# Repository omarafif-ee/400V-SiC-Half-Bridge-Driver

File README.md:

# 400 V SiC MOSFET Isolated Half-Bridge Gate Driver PCB

## Overview

**Objective:** To design a two-layer PCB for an isolated 400 V SiC MOSFET half-bridge gate driver using the UCC21520DW, with appropriate isolation, gate-drive control, and dead time. The design will be checked in KiCad and its switching behaviour verified through LTspice simulation.

This project covers the design and simulation of a 400 V isolated half-bridge gate driver using KiCad 10.0 and LTspice 26.1. A Texas Instruments UCC21520DW isolated dual-channel gate driver controls two Wolfspeed C3M0120090D 900 V SiC MOSFETs.

📄 **[Read the Full Technical Report (PDF)](Documentation/Technical%20Report%20-%20400V%20SiC%20MOSFET%20Isolated%20Half-Bridge%20Gate%20Driver%20PCB.pdf)**

---

## System Block Diagram

The 5 V PWM inputs (PWM-A and PWM-B) are separated from the 400 V power stage by the 5.7 kVrms isolation barrier inside the UCC21520DW. On the secondary side, the driver switches Q1 and Q2 across the 400 V DC rail and GNDPWR to swing SW_NODE between 0 V and 400 V, using a bootstrap network to power the floating high-side drive.

---

## Key Specifications

- DC bus voltage: 400 V DC
- Power switches: 2 × Wolfspeed C3M0120090D 900 V SiC MOSFETs in TO-247-3 packages
- Gate driver: Texas Instruments UCC21520DW, with a stated isolation rating of 5.7 kVrms
- Gate-drive supply: +15 V, with a bootstrap network for the floating high-side supply
- Hardware dead time: Approximately 220 ns, set using R1 = 22 kΩ
- PCB: Two copper layers
- High-voltage clearance rule: Custom KiCad design rule set to 2.9 mm for DC_PLUS and SW_NODE against other nets, with an exception for connections within the same floating high-side section

---

## Hardware Design and PCB Layout

### 1. Schematic

The UCC21520DW isolates the logic ground (GND) from the power-side connections (GNDPWR and SW_NODE). The low-side MOSFET is referenced to ground, while the high-side driver floats with SW_NODE.

When the low-side MOSFET turns on and SW_NODE falls to 0 V, the +15 V rail charges bootstrap capacitors C4 and C5 through resistor R8 and diode D1. When the high-side switch turns on, D1 becomes reverse-biased and the capacitors supply the floating driver at about 14 V (accounting for a 1 V diode drop).

The gate resistors use separate paths for turn-on and turn-off. The 10 Ω resistors (R2 and R5) control gate charging, while the Schottky diodes (D2 and D3) and 1 Ω resistors (R3 and R6) provide a lower-resistance turn-off path (~0.91 Ω in parallel) to discharge the gate quickly. The 10 kΩ pull-down resistors (R4 and R7) keep the gates near 0 V when unpowered.

Resistor R1 (22 kΩ) sets the dead time to about 220 ns, with capacitor C3 placed in parallel to filter noise. Capacitor C8 (100 nF, 630 V) is placed near the MOSFETs to absorb switching transients, and two 220 kΩ resistors (R9 and R10) are placed in series as bleeders so each sees 200 V.

### 2. Two-Layer PCB Layout

The logic section is placed on the left and the power stage on the right. No traces are routed beneath U1, leaving more than 8 mm of separation between the logic and high-voltage sides. The layout was checked in KiCad against the 2.9 mm high-voltage clearance rule until no DRC errors remained.

Because the MOSFET pins have a 5.45 mm centre-to-centre spacing, the DC_PLUS, SW_NODE, and GNDPWR traces narrow to 1.5 mm near the pads before widening to 2.0 mm. SW_NODE is routed on the top layer between C8 and the R9/R10 midpoint without extra vias. C8, R9/R10, and J3 are kept near Q1 and Q2 to shorten the switching path and reduce parasitic inductance.

---

## LTspice Simulation

The secondary-side half-bridge was simulated in LTspice over 20 µs (two switching periods at 100 kHz). To avoid convergence problems, the UCC21520DW and bootstrap circuit were replaced with pulse voltage sources (0–14 V referenced to SW_NODE for the high side, and 15–0 V referenced to ground for the low side, with 15 ns rise/fall times and 220 ns dead time).

The model uses a 400 V supply (0.05 Ω series resistance), a 20 nH supply-loop inductance, a 200 µH inductive load (20 Ω series resistance), and a custom VDMOS model for the C3M0120090D.

### Results

| Objective | Achieved result |
|:---|:---|
| 1. Design a PCB for a 400 V half-bridge | A two-layer KiCad PCB was designed for two 900 V SiC MOSFETs. |
| 2. Separate the control and power sections | The layout keeps copper out from beneath the gate driver and maintains more than 8 mm of spacing between the logic and high-voltage sides. |
| 3. Set suitable dead time to prevent shoot-through | A 22 kΩ resistor sets approximately 220 ns dead time. No shoot-through was observed in the LTspice simulation. |
| 4. Provide suitable gate drive for both MOSFETs | The simulation showed approximately 14 V gate-to-source drive for the high-side MOSFET and 15 V for the low-side MOSFET. |
| 5. Check switching behaviour at 400 V | The simulated switching node transitions between approximately 0 V and 400 V over two 100 kHz periods. |
| 6. Check for unwanted turn-on caused by the Miller effect | Simulated low-side gate bounce was approximately 0.7–0.8 V, below the 1.8 V threshold used in the report for comparison. |

The simulation results confirm that the intended timing, drive voltages, and isolation are achieved under ideal models, although hardware testing will be required to evaluate physical ringing and thermal performance on a fabricated PCB.

---

## Bill of Materials (BOM)

| Ref. | Qty. | Value / Role | Footprint | Manufacturer | Part Number (MPN) |
|:---|:---:|:---|:---|:---|:---|
| U1 | 1 | Isolated gate driver | SOIC-16W | Texas Instruments | UCC21520DW |
| Q1, Q2 | 2 | 900 V SiC MOSFET | TO-247-3 | Wolfspeed | C3M0120090D |
| D1 | 1 | Bootstrap diode | DO-41 axial | Generic | UF4007 |
| D2, D3 | 2 | Gate turn-off diode | SOD-123 SMD | Generic | 1N5819HW |
| C8 | 1 | 100 nF snubber capacitor, 630 V | Radial, 15 mm pitch | WIMA | MKP1J031004B00KSSD |
| R9, R10 | 2 | 220 kΩ bleeder resistor | 0207 axial | Yageo | MFR-25FTE52-220K |
| R1 | 1 | 22 kΩ dead-time resistor | 0805 SMD | Yageo | RC0805FR-0722KL |
| R2, R5 | 2 | 10 Ω turn-on resistor | 0805 SMD | Yageo | RC0805FR-0710RL |
| R3, R6 | 2 | 1 Ω turn-off resistor | 0805 SMD | Yageo | RC0805FR-071RL |
| R4, R7 | 2 | 10 kΩ gate pull-down resistor | 0805 SMD | Yageo | RC0805FR-0710KL |
| R8 | 1 | 2.2 Ω bootstrap charging resistor | 0805 SMD | Yageo | RC0805FR-072R2L |
| C1, C4, C6 | 3 | 100 nF decoupling capacitor | 0805 SMD | Murata | GRM21BR71H104KA01L |
| C2, C5, C7 | 3 | 1 µF supply capacitor | 0805 SMD | Murata | GRM21BR71H105KA12L |
| C3 | 1 | 2.2 nF dead-time filter capacitor | 0805 SMD | Murata | GRM21BR71H222KA01L |
| J3 | 1 | High-voltage terminal header, 1×03, 7.62 mm pitch | GMSTBA 1×03 | Phoenix Contact | 1766246 |
| J1, J2 | 2 | Low-voltage headers, 1×02 and 1×04 | 2.54 mm pitch | Generic | 1×02 and 1×04 male headers |

---

## Design Limitations and Possible Improvements

1. Shorter trace paths: The current board uses wide spacing for straightforward routing, making some connections between U1, the MOSFETs, and C8 longer than ideal. Moving components closer and using copper pours would reduce stray inductance and ringing.
2. Bipolar gate supply (-4 V / +15 V): The 1 V drop across D1 lowers the high-side gate drive to ~14 V, and real hardware could experience higher gate bounce than the simulated 0.8 V. Replacing the bootstrap circuit with an isolated bipolar supply (-4 V / +15 V) would address both issues.
3. Shorter dead time: Reducing R1 from 22 kΩ to 10 kΩ would shorten dead time from 220 ns to ~100 ns, reducing body-diode conduction losses once hardware testing confirms no shoot-through.

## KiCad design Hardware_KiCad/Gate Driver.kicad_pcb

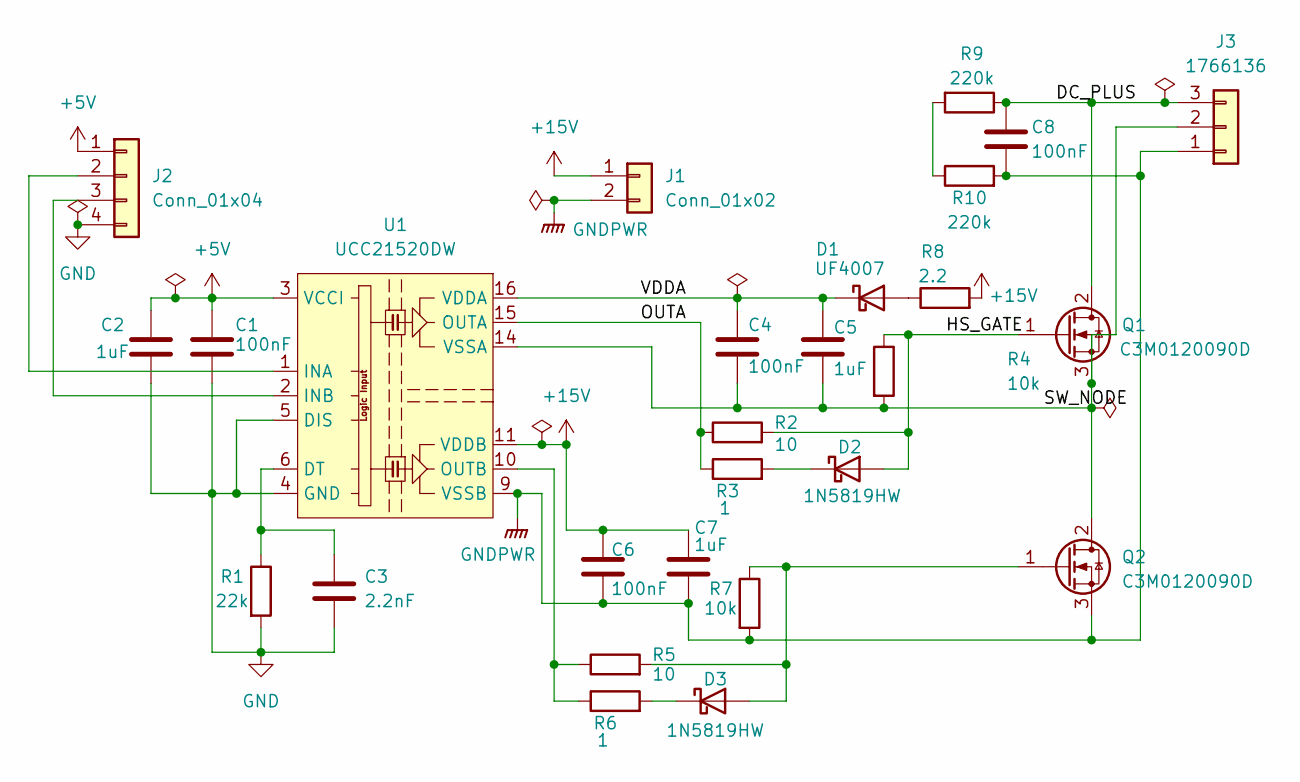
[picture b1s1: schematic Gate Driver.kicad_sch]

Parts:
C1, C4, C6: 100nF; C_0805_2012Metric; Part Number GRM21BR71H104KA01L
C2, C5, C7: 1uF; C_0805_2012Metric; Part Number GRM21BR71H105KA12L
C3: 2.2nF; C_0805_2012Metric; Part Number GRM21BR71H222KA01L
C8: 100nF; C_Rect_L18.0mm_W6.0mm_P15.00mm_FKS3_FKP3; Part Number MKP1J031004B00KSSD
D1: UF4007; D_DO-41_SOD81_P10.16mm_Horizontal; Part Number UF4007
D2, D3: 1N5819HW; D_SOD-123; Part Number 1N5819HW
J1: Conn_01x02; PinHeader_1x02_P2.54mm_Vertical; Part Number 1x02 Male Header 2.54mm
J2: Conn_01x04; PinHeader_1x04_P2.54mm_Vertical; Part Number 1x04 Male Header 2.54mm
J3: 1766136; PhoenixContact_GMSTBA_2,5_3-G-7,62_1x03_P7.62mm_Horizontal; Part Number 1766246
Q1, Q2: C3M0120090D; TO-247-3_Vertical; Part Number C3M0120090D
R1: 22k; R_0805_2012Metric; Part Number RC0805FR-0722KL
R2, R5: 10; R_0805_2012Metric; Part Number RC0805FR-0710RL
R3, R6: 1; R_0805_2012Metric; Part Number RC0805FR-071RL
R4, R7: 10k; R_0805_2012Metric; Part Number RC0805FR-0710KL
R8: 2.2; R_0805_2012Metric; Part Number RC0805FR-072R2L
R9, R10: 220k; R_Axial_DIN0207_L6.3mm_D2.5mm_P10.16mm_Horizontal; Part Number MFR-25FTE52-220K
U1: UCC21520DW; SOIC-16W_7.5x10.3mm_P1.27mm; Part Number UCC21520DW

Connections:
+5V: C1.1, C2.1, J2.1, U1.3 (VCCI), U1.8 (VCCI)
+15V: C6.1, C7.1, J1.1, R8.2, U1.11 (VDDB)
/DC_PLUS: C8.1, J3.3, Q1.2 (D), R9.1
/HS_GATE: D2.2 (A), Q1.1 (G), R2.2, R4.1
/OUTA: R2.1, R3.1, U1.15 (OUTA)
/SW_NODE: C4.2, C5.2, J3.2, Q1.3 (S), Q2.2 (D), R4.2, U1.14 (VSSA)
/VDDA: C4.1, C5.1, D1.1 (K), U1.16 (VDDA)
GND: C1.2, C2.2, C3.2, J2.4, R1.2, U1.4 (GND), U1.5 (DIS)
GNDPWR: C6.2, C7.2, C8.2, J1.2, J3.1, Q2.3 (S), R7.2, R10.2, U1.9 (VSSB)
unnamed: D1.2 (A), R8.1
unnamed: D2.1 (K), R3.2
unnamed: D3.2 (A), Q2.1 (G), R5.2, R7.1
unnamed: D3.1 (K), R6.2
unnamed: J2.2, U1.1 (INA)
unnamed: J2.3, U1.2 (INB)
unnamed: R9.2, R10.1
unnamed: C3.1, R1.1, U1.6 (DT)
unnamed: R5.1, R6.1, U1.10 (OUTB)

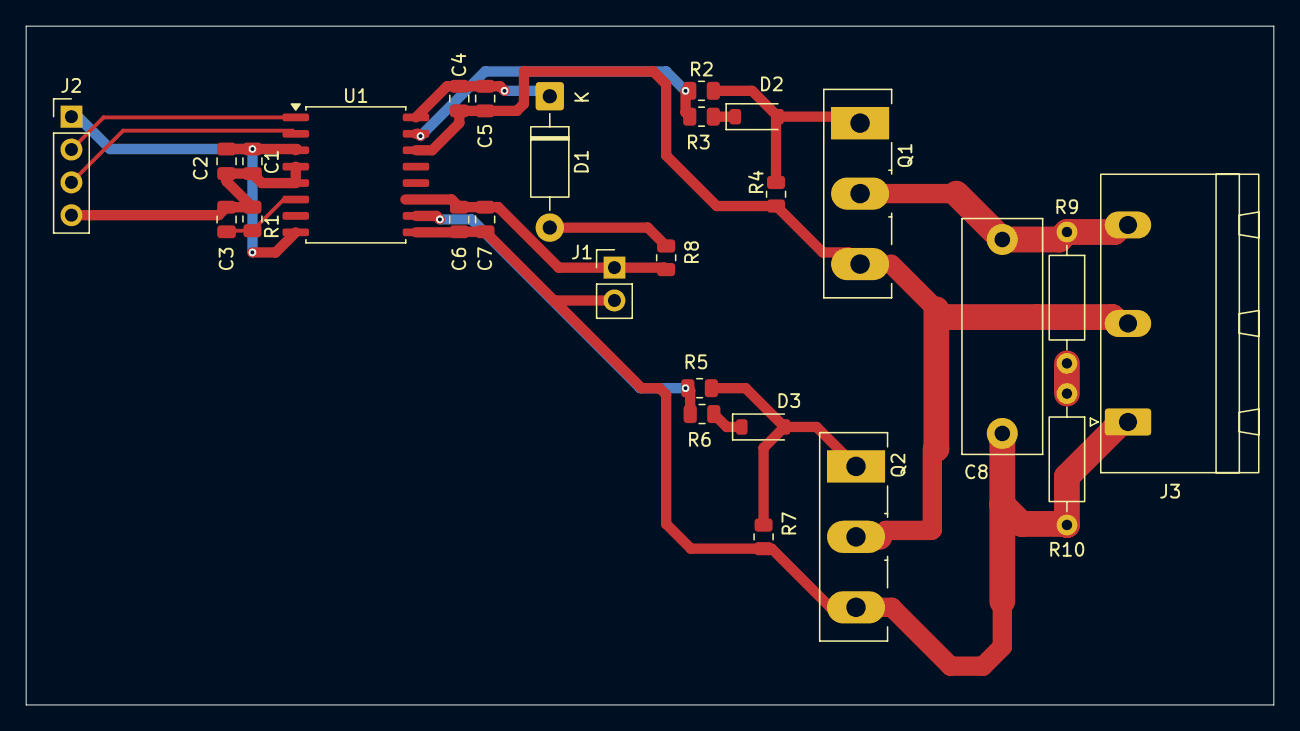
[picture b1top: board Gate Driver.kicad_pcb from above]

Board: 2 copper layers, 96.5 x 52.5 mm, 27 parts (0 on the bottom side), 18 nets.

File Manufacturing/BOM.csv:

Reference,Qty,Value,Exclude from Position Files,Footprint,Datasheet,#,Part Number,Manufacturer
"C1,C4,C6",3,100nF,${EXCLUDE_FROM_POS_FILES},Capacitor_SMD:C_0805_2012Metric,,1,GRM21BR71H104KA01L,Murata
"C2,C5,C7",3,1uF,${EXCLUDE_FROM_POS_FILES},Capacitor_SMD:C_0805_2012Metric,,2,GRM21BR71H105KA12L,Murata
C3,1,2.2nF,${EXCLUDE_FROM_POS_FILES},Capacitor_SMD:C_0805_2012Metric,,3,GRM21BR71H222KA01L,Murata
C8,1,100nF,${EXCLUDE_FROM_POS_FILES},Capacitor_THT:C_Rect_L18.0mm_W6.0mm_P15.00mm_FKS3_FKP3,,4,MKP1J031004B00KSSD,WIMA
D1,1,UF4007,${EXCLUDE_FROM_POS_FILES},Diode_THT:D_DO-41_SOD81_P10.16mm_Horizontal,,5,UF4007,Generic
"D2,D3",2,1N5819HW,${EXCLUDE_FROM_POS_FILES},Diode_SMD:D_SOD-123,,6,1N5819HW,Generic
J1,1,Conn_01x02,${EXCLUDE_FROM_POS_FILES},Connector_PinHeader_2.54mm:PinHeader_1x02_P2.54mm_Vertical,,7,1x02 Male Header 2.54mm,Generic
J2,1,Conn_01x04,${EXCLUDE_FROM_POS_FILES},Connector_PinHeader_2.54mm:PinHeader_1x04_P2.54mm_Vertical,,8,1x04 Male Header 2.54mm,Generic
J3,1,1766136,${EXCLUDE_FROM_POS_FILES},"Connector_Phoenix_GMSTB:PhoenixContact_GMSTBA_2,5_3-G-7,62_1x03_P7.62mm_Horizontal",,9,1766246,Phoenix Contact
"Q1,Q2",2,C3M0120090D,${EXCLUDE_FROM_POS_FILES},Package_TO_SOT_THT:TO-247-3_Vertical,,10,C3M0120090D,Wolfspeed
R1,1,22k,${EXCLUDE_FROM_POS_FILES},Resistor_SMD:R_0805_2012Metric,,11,RC0805FR-0722KL,Yageo
"R2,R5",2,10,${EXCLUDE_FROM_POS_FILES},Resistor_SMD:R_0805_2012Metric,,12,RC0805FR-0710RL,Yageo
"R3,R6",2,1,${EXCLUDE_FROM_POS_FILES},Resistor_SMD:R_0805_2012Metric,,13,RC0805FR-071RL,Yageo
"R4,R7",2,10k,${EXCLUDE_FROM_POS_FILES},Resistor_SMD:R_0805_2012Metric,,14,RC0805FR-0710KL,Yageo
R8,1,2.2,${EXCLUDE_FROM_POS_FILES},Resistor_SMD:R_0805_2012Metric,,15,RC0805FR-072R2L,Yageo
"R9,R10",2,220k,${EXCLUDE_FROM_POS_FILES},Resistor_THT:R_Axial_DIN0207_L6.3mm_D2.5mm_P10.16mm_Horizontal,,16,MFR-25FTE52-220K,Yageo
U1,1,UCC21520DW,${EXCLUDE_FROM_POS_FILES},Package_SO:SOIC-16W_7.5x10.3mm_P1.27mm,http://www.ti.com/lit/ds/symlink/ucc21520.pdf,17,UCC21520DW,Texas Instruments
